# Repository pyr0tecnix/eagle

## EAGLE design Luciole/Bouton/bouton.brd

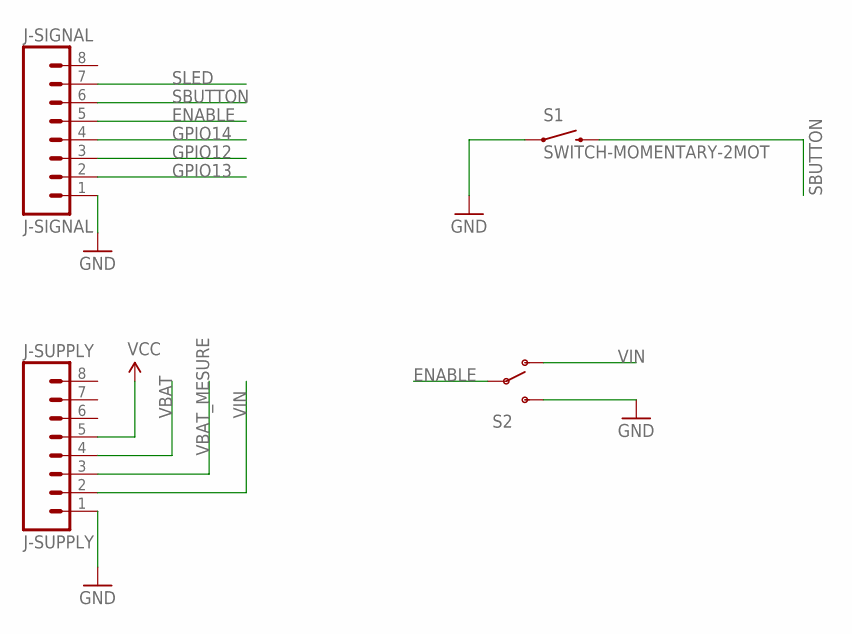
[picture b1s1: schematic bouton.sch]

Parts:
J-SIGNAL: J-SIGNAL; 1X08_ROUND
J-SUPPLY: J-SUPPLY; 1X08_ROUND
S1: SWITCH-MOMENTARY-2MOT; TACTILE-PTH
S2: SWITCH-SPDTSMD2; SWITCH-SPDT-SMD

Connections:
ENABLE: J-SIGNAL.5, S2.2
GND: J-SIGNAL.1, J-SUPPLY.1, S1.1, S2.3 (S)
GPIO12: J-SIGNAL.3
GPIO13: J-SIGNAL.2
GPIO14: J-SIGNAL.4
SBUTTON: J-SIGNAL.6, S1.4 (2)
SLED: J-SIGNAL.7
VBAT: J-SUPPLY.4
VBAT_MESURE: J-SUPPLY.3
VCC: J-SUPPLY.5
VIN: J-SUPPLY.2, S2.1 (O)

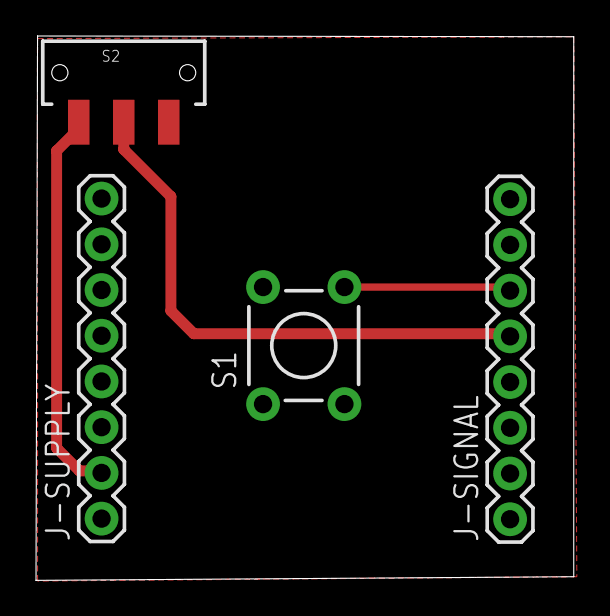
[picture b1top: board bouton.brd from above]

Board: 2 copper layers, 29.9 x 30.2 mm, 4 parts (0 on the bottom side), 4 nets.

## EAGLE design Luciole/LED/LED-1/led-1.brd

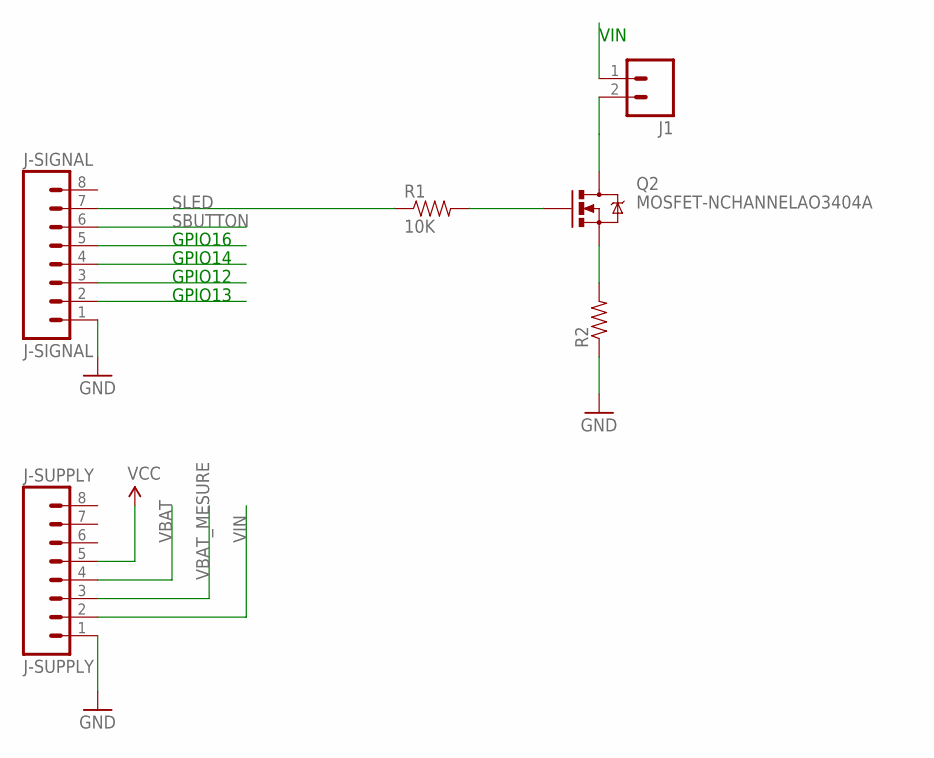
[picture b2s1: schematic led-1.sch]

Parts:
J1: M02JST-PTH-VERT; JST-2-PTH-VERT
J-SIGNAL: J-SIGNAL; 1X08_ROUND
J-SUPPLY: J-SUPPLY; 1X08_ROUND
Q2: MOSFET-NCHANNELAO3404A; SOT23-3
R1: 10K; 0805
R2: RESISTORPTH-1/2W; AXIAL-0.5

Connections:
GND: J-SIGNAL.1, J-SUPPLY.1, R2.P$1 (1)
GPIO12: J-SIGNAL.3
GPIO13: J-SIGNAL.2
GPIO14: J-SIGNAL.4
GPIO16: J-SIGNAL.5
unnamed: Q2.2 (S), R2.P$2 (2)
unnamed: Q2.1 (G), R1.2
unnamed: J1.2, Q2.3 (D)
SBUTTON: J-SIGNAL.6
SLED: J-SIGNAL.7, R1.1
VBAT: J-SUPPLY.4
VBAT_MESURE: J-SUPPLY.3
VCC: J-SUPPLY.5
VIN: J1.1, J-SUPPLY.2

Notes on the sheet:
GPIO13
GPIO12
GPIO14
GPIO16
VIN

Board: 2 copper layers, 6 parts (0 on the bottom side), 6 nets, no tracks yet.

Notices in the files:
parts and their libraries:
SparkFun-Connectors: Licensing: Creative Commons ShareAlike 4.0 International - https://creativecommons.org/licenses/by-sa/4.0
